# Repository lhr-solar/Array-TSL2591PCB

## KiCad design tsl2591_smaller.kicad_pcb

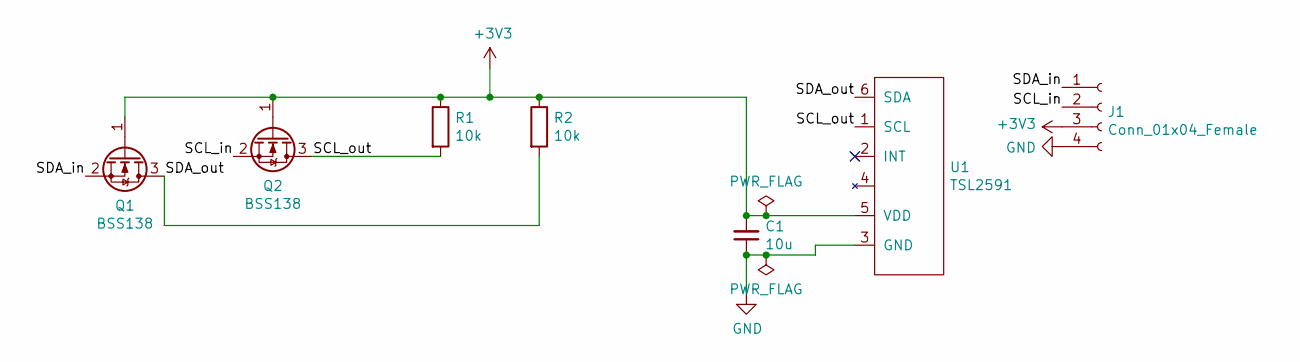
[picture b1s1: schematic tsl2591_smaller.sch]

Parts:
C1: 10u; R_0805
J1: Conn_01x04_Female; PinHeader_2x02_P2.54mm_Vertical_SMD
Q1, Q2: BSS138; SOT-23
R1, R2: 10k; R_0805
U1: TSL2591; tsl2591

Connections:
+3V3: C1.2, J1.3, Q1.1 (G), Q2.1 (G), R1.1, R2.1, U1.5 (VDD)
/SCL_in: J1.2, Q2.2 (S)
/SCL_out: Q2.3 (D), R1.2, U1.1 (SCL)
/SDA_in: J1.1, Q1.2 (S)
/SDA_out: Q1.3 (D), R2.2, U1.6 (SDA)
GND: C1.1, J1.4, U1.3 (GND)

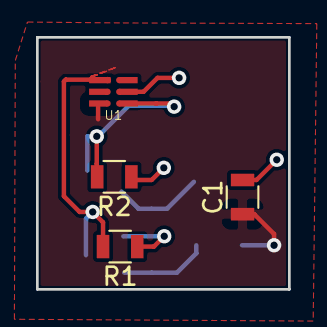
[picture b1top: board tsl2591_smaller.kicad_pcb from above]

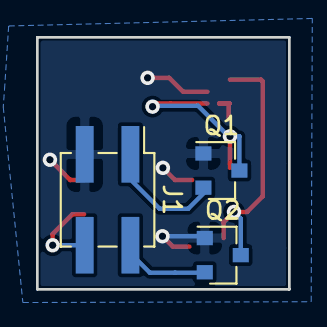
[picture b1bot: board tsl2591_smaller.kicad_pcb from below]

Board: 2 copper layers, 14.0 x 14.0 mm, 7 parts (3 on the bottom side), 6 nets.

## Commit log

2021-03-06 1st iteration
    Removed some components from the Adafruit design to fit in a smaller footprint
2021-03-06 Removed more components
